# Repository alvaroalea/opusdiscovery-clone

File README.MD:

# The Opus Discovery mini-clone Disk Interface for ZX Spectrum

UNDER LICENSE GPL Version 3

the schematic and PCB for this interfaz, make in KICAD
target is to have a PCB is less than 10x10cm so it's very cheap.

WARNING - THIS IS WORK IN PROGRESS - NOT TESTED

The Advantage of this interfaz over the original are:

- 4 Banks of ROM, so you can swap between original ROM and Quickdos, selectable by dip-switches, in the roms directory you can found it individually and one file ready to burn into a 28C256 flashrom.

- Included Fixed for +2A/+3, so can be used in any ZX Spectrum, selection by jumpers, compatibility with +2A/+3 is not yet tested.

- Reset Button

- Posibility of use crossed and plain floppy cable, and invert Drive 1 and Drive 2, very usefull if you have a Gotek and a real floppy.
With plain floppy cable you can use up to 4 drives.

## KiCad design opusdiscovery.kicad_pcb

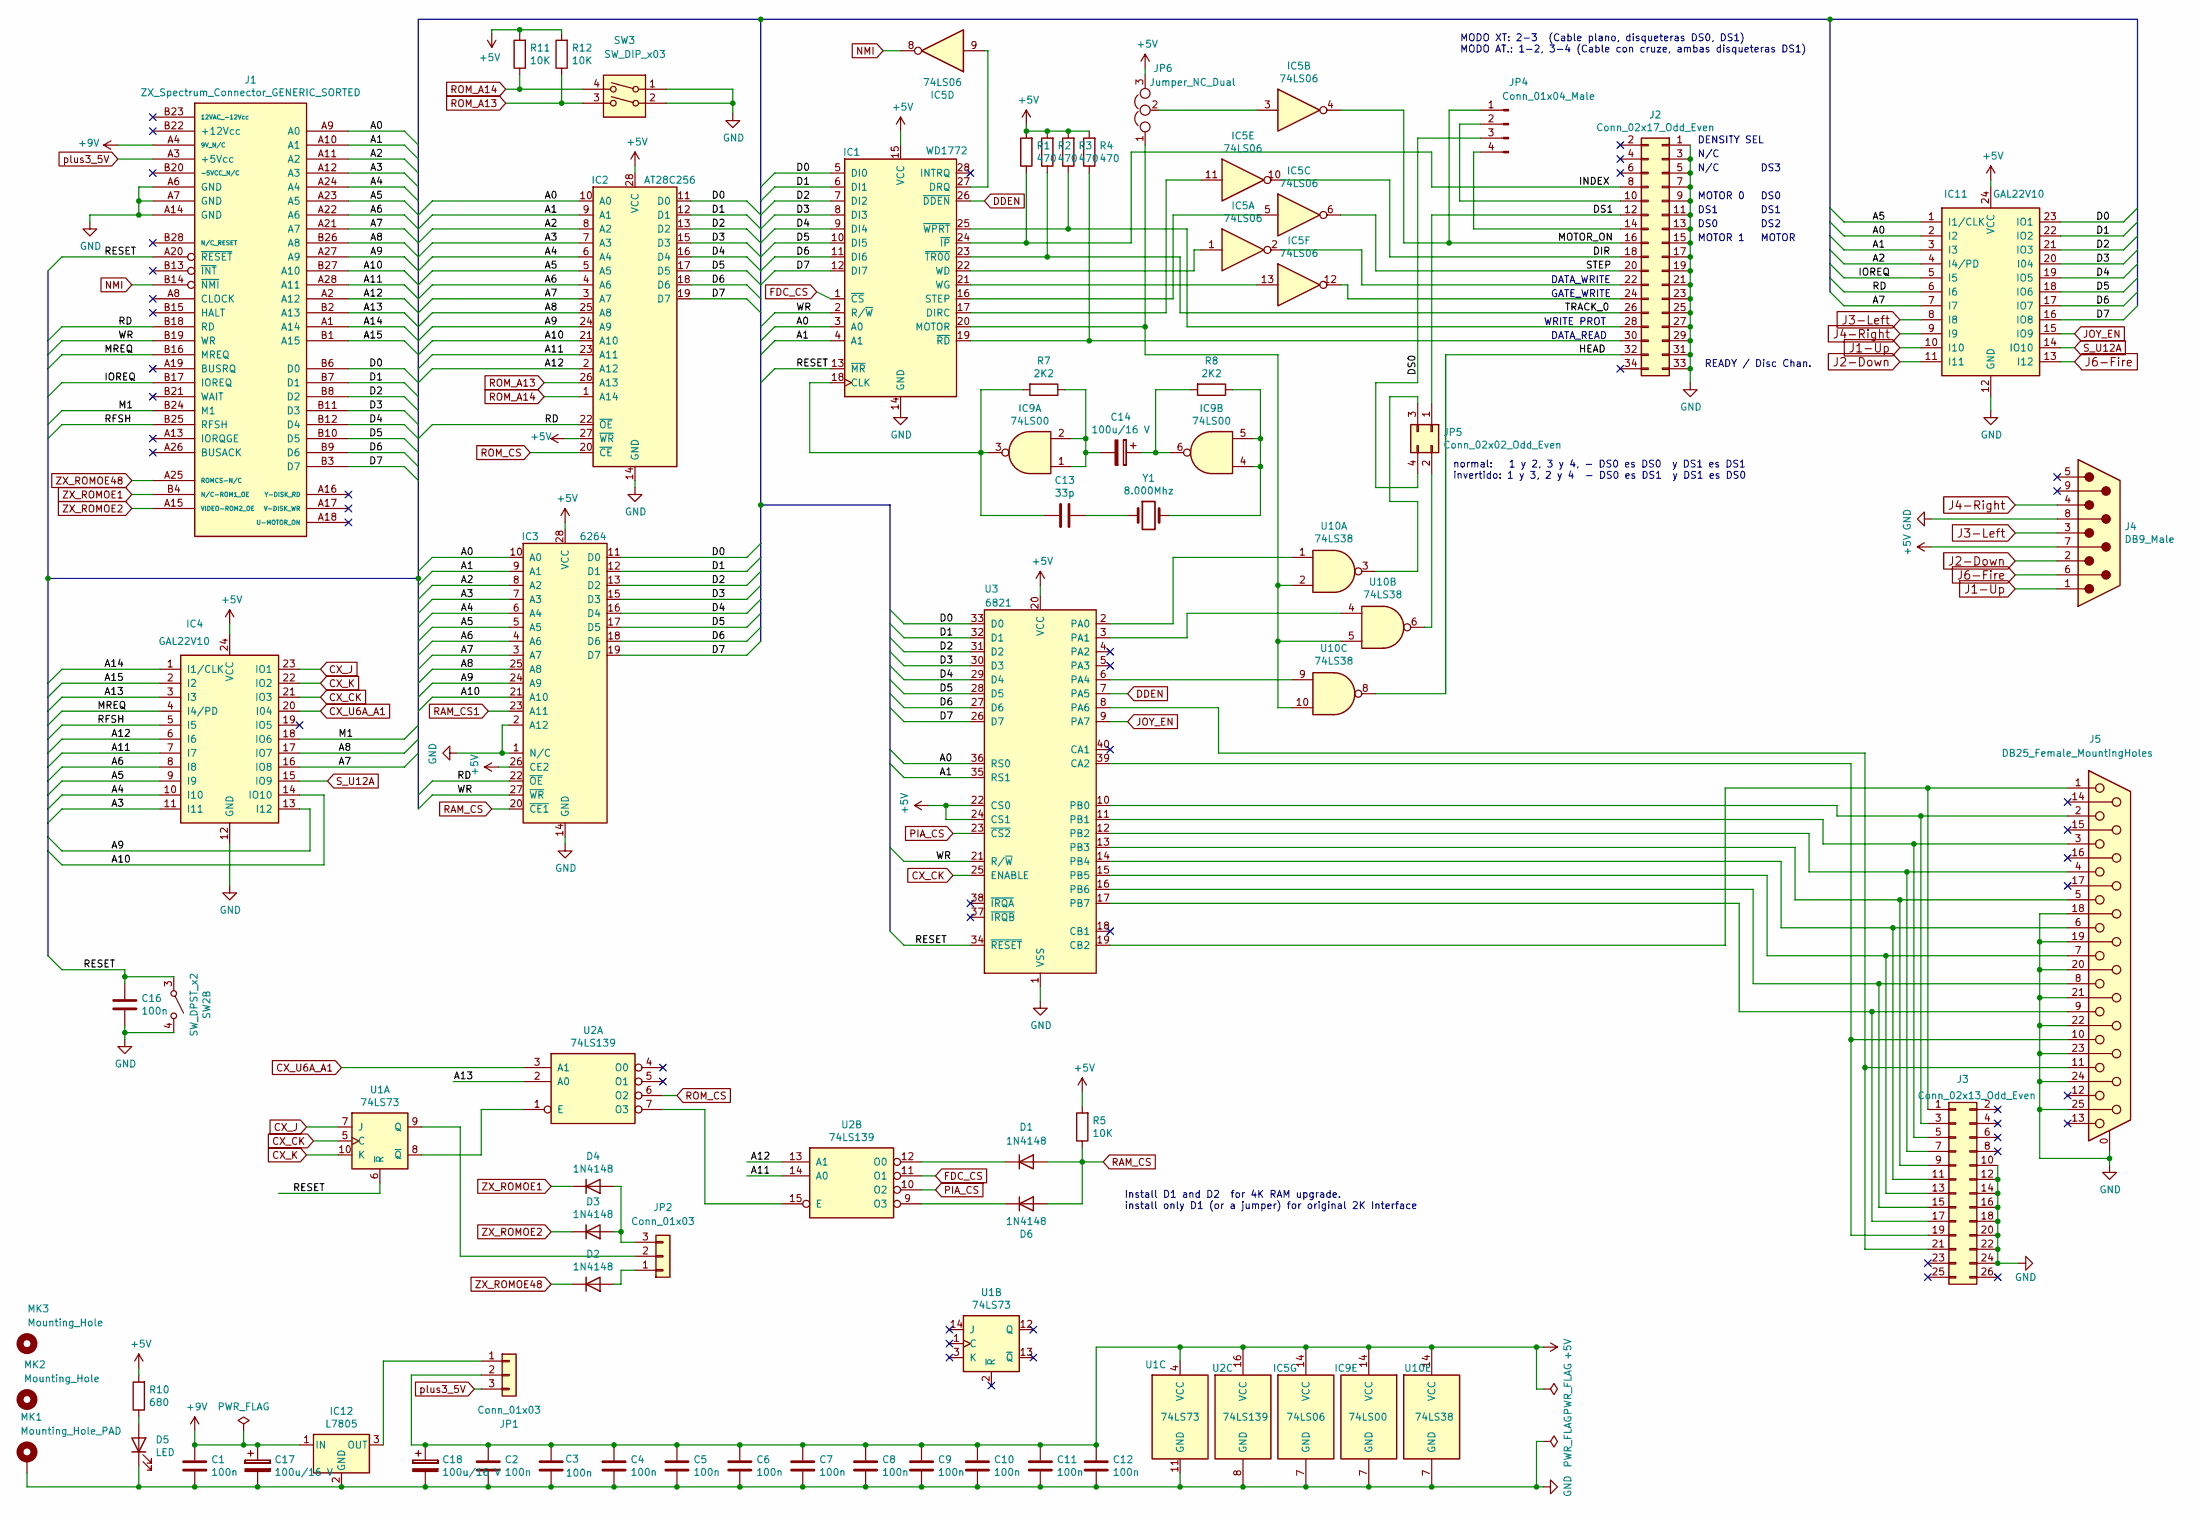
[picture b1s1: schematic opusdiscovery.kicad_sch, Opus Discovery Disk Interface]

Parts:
C1, C2, C3, C4, C5, C6, C7, C8, C9, C10, C11, C12, C16: 100n; C_Disc_D5.0mm_W2.5mm_P5.00mm
C13: 33p; C_Disc_D5.0mm_W2.5mm_P5.00mm
C14, C17, C18: 100u/16 V; CP_Radial_D7.5mm_P2.50mm
D1, D2, D3, D4, D6: 1N4148; D_DO-35_SOD27_P7.62mm_Horizontal
D5: LED; LED_D5.0mm
IC1: WD1772; DIP-28_W15.24mm_LongPads
IC2: AT28C256; DIP-28_W15.24mm_LongPads
IC3: 6264; DIP-28_W15.24mm_LongPads
IC4, IC11: GAL22V10; DIP-24_W7.62mm_LongPads
IC5: 74LS06; DIP-14_W7.62mm_LongPads
IC9: 74LS00; DIP-14_W7.62mm_LongPads
IC12: L7805; TO-220-3_Vertical
J1: ZX_Spectrum_Connector_GENERIC_SORTED; ZX_CONN
J2: Conn_02x17_Odd_Even; PinHeader_2x17_P2.54mm_Vertical
J3: Conn_02x13_Odd_Even; PinHeader_2x13_P2.54mm_Vertical
J4: DB9_Male; DSUB-9_Male_Horizontal_P2.77x2.84mm_EdgePinOffset4.94mm_Hou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
J5: DB25_Female_MountingHoles; DSUB-25_Female_Horizontal_P2.77x2.84mm_EdgePinOffset4.94mm_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
JP1, JP2: Conn_01x03; PinHeader_1x03_P2.54mm_Vertical
JP4: Conn_01x04_Male; PinHeader_1x04_P2.54mm_Vertical
JP5: Conn_02x02_Odd_Even; PinHeader_2x02_P2.54mm_Vertical
JP6: Jumper_NC_Dual; SolderJumper-3_P1.3mm_Bridged12_RoundedPad1.0x1.5mm
MK1: Mounting_Hole_PAD; MountingHole_3mm_Pad_Via
MK2, MK3: Mounting_Hole; MountingHole_3mm
R1, R2, R3, R4: 470; R_Axial_DIN0207_L6.3mm_D2.5mm_P7.62mm_Horizontal
R5, R11, R12: 10K; R_Axial_DIN0207_L6.3mm_D2.5mm_P7.62mm_Horizontal
R7, R8: 2K2; R_Axial_DIN0207_L6.3mm_D2.5mm_P7.62mm_Horizontal
R10: 680; R_Axial_DIN0207_L6.3mm_D2.5mm_P7.62mm_Horizontal
SW2: SW_DPST_x2; SW_TH_Tactile_Omron_B3F-10xx
SW3: SW_DIP_x03; SW_DIP_SPSTx02_Slide_6.7x6.64mm_W7.62mm_P2.54mm_LowProfile
U1: 74LS73; DIP-14_W7.62mm_LongPads
U2: 74LS139; DIP-16_W7.62mm_LongPads
U3: 6821; DIP-40_W15.24mm_LongPads
U10: 74LS38; DIP-14_W7.62mm_LongPads
Y1: 8.000Mhz; Crystal_HC18-U_Vertical

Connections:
+5V: C2.2, C3.2, C4.2, C5.2, C6.2, C7.2, C8.2, C9.2, C10.2, C11.2, C12.2, C18.1, IC1.15 (VCC), IC2.27 (~WR), IC2.28 (VCC), IC3.26 (CE2), IC3.28 (VCC), IC4.24 (VCC), IC5.14 (VCC), IC9.14 (VCC), IC11.24 (VCC), J4.7, JP1.2, JP6.3, R1.2, R2.2, R3.2, R4.2, R5.2, R10.2, R11.2, R12.2, U1.4 (VCC), U2.16 (VCC), U3.20 (VCC), U3.22 (CS0), U3.24 (CS1), U10.14 (VCC)
+9V: C1.2, C17.1, IC12.1 (IN), J1.A4 (9V_N/C)
/A0: IC1.3 (A0), IC2.10 (A0), IC3.10 (A0), IC11.2 (I2), J1.A9 (A0), U3.36 (RS0)
/A1: IC1.4 (A1), IC2.9 (A1), IC3.9 (A1), IC11.3 (I3), J1.A10 (A1), U3.35 (RS1)
/A2: IC2.8 (A2), IC3.8 (A2), IC11.4 (I4/PD), J1.A11 (A2)
/A3: IC2.7 (A3), IC3.7 (A3), IC4.11 (I11), J1.A12 (A3)
/A4: IC2.6 (A4), IC3.6 (A4), IC4.10 (I10), J1.A24 (A4)
/A5: IC2.5 (A5), IC3.5 (A5), IC4.9 (I9), IC11.1 (I1/CLK), J1.A23 (A5)
/A6: IC2.4 (A6), IC3.4 (A6), IC4.8 (I8), J1.A22 (A6)
/A7: IC2.3 (A7), IC3.3 (A7), IC4.16 (IO8), IC11.7 (I7), J1.A21 (A7)
/A8: IC2.25 (A8), IC3.25 (A8), IC4.17 (IO7), J1.B26 (A8)
/A9: IC2.24 (A9), IC3.24 (A9), IC4.13 (I12), J1.A27 (A9)
/A10: IC2.21 (A10), IC3.21 (A10), IC4.14 (IO10), J1.B27 (A10)
/A11: IC2.23 (A11), IC4.7 (I7), J1.A28 (A11), U2.14 (A0)
/A12: IC2.2 (A12), IC4.6 (I6), J1.A2 (A12), U2.13 (A1)
/A13: IC4.3 (I3), J1.B2 (A13), U2.2 (A0)
/A14: IC4.1 (I1/CLK), J1.A1 (A14)
/A15: IC4.2 (I2), J1.B1 (A15)
/D0: IC1.5 (DI0), IC2.11 (D0), IC3.11 (D0), IC11.23 (IO1), J1.B6 (D0), U3.33 (D0)
/D1: IC1.6 (DI1), IC2.12 (D1), IC3.12 (D1), IC11.22 (IO2), J1.B7 (D1), U3.32 (D1)
/D2: IC1.7 (DI2), IC2.13 (D2), IC3.13 (D2), IC11.21 (IO3), J1.B8 (D2), U3.31 (D2)
/D3: IC1.8 (DI3), IC2.15 (D3), IC3.15 (D3), IC11.20 (I04), J1.B11 (D3), U3.30 (D3)
/D4: IC1.9 (DI4), IC2.16 (D4), IC3.16 (D4), IC11.19 (IO5), J1.B12 (D4), U3.29 (D4)
/D5: IC1.10 (DI5), IC2.17 (D5), IC3.17 (D5), IC11.18 (IO6), J1.B10 (D5), U3.28 (D5)
/D6: IC1.11 (DI6), IC2.18 (D6), IC3.18 (D6), IC11.17 (IO7), J1.B9 (D6), U3.27 (D6)
/D7: IC1.12 (DI7), IC2.19 (D7), IC3.19 (D7), IC11.16 (IO8), J1.B3 (D7), U3.26 (D7)
/DIR: IC5.10, J2.18
/DS0: JP4.3, JP5.4
/DS1: J2.12, JP5.1
/HEAD: J2.32, U10.8
/INDEX: IC1.24 (~IP), J2.8, R1.1
/IOREQ: IC11.5 (I5), J1.B17 (IOREQ)
/M1: IC4.18 (IO6), J1.B24 (M1)
/MOTOR_ON: IC5.4, J2.16, JP4.1
/MREQ: IC4.4 (I4/PD), J1.B16 (MREQ)
/RD: IC2.22 (~OE), IC3.22 (~OE), IC11.6 (I6), J1.B18 (RD)
/RESET: C16.2, IC1.13 (~MR), J1.A20 (~RESET), SW2.3 (A), U1.6 (~R), U3.34 (~RESET)
/RFSH: IC4.5 (I5), J1.B25 (RFSH)
/STEP: IC5.6, J2.20
/TRACK_0: IC1.23 (~TR00), J2.26, R2.1
/WR: IC1.2 (R/~W), IC3.27 (~WR), J1.B19 (WR), U3.21 (R/~W)
CX_CK: IC4.21 (IO3), U1.5 (C), U3.25 (ENABLE)
CX_J: IC4.23 (IO1), U1.7 (J)
CX_K: IC4.22 (IO2), U1.10 (K)
CX_U6A_A1: IC4.20 (I04), U2.3 (A1)
DDEN: IC1.26 (~DDEN), U3.7 (PA5)
FDC_CS: IC1.1 (~CS), U2.11 (O1)
GND: C1.1, C2.1, C3.1, C4.1, C5.1, C6.1, C7.1, C8.1, C9.1, C10.1, C11.1, C12.1, C16.1, C17.2, C18.2, D5.1 (K), IC1.14 (GND), IC2.14 (GND), IC3.1 (N/C), IC3.2 (A12), IC3.14 (GND), IC4.12 (GND), IC5.7 (GND), IC9.7 (GND), IC11.12 (GND), IC12.2 (GND), J1.A6 (GND), J1.A7 (GND), J1.A14 (GND), J2.1, J2.3, J2.5, J2.7, J2.9, J2.11, J2.13, J2.15, J2.17, J2.19, J2.21, J2.23, J2.25, J2.27, J2.29, J2.31, J2.33, J3.10, J3.12, J3.14, J3.16, J3.18, J3.20, J3.22, J3.24, J4.8, J5.0 (PAD), J5.18, J5.19, J5.20, J5.21, J5.22, J5.23, J5.24, J5.25, MK1.1, SW2.4 (B), SW3.1, SW3.2, U1.11 (GND), U2.8 (GND), U3.1 (VSS), U10.7 (GND)
J1-Up: IC11.10 (I10), J4.1
J2-Down: IC11.11 (I11), J4.2
J3-Left: IC11.8 (I8), J4.3
J4-Right: IC11.9 (I9), J4.4
J6-Fire: IC11.13 (I12), J4.6
JOY_EN: IC11.15 (IO9), U3.9 (PA7)
NMI: IC5.8, J1.B14 (~NMI)
unnamed: C13.1, Y1.1
unnamed: C13.2, IC1.18 (CLK), IC9.3, R7.2
unnamed: C14.1, IC9.6, R8.2
unnamed: C14.2, IC9.1, IC9.2, R7.1
unnamed: D2.2 (A), JP2.1
unnamed: D3.2 (A), D4.2 (A), JP2.3
unnamed: D5.2 (A), R10.1
unnamed: IC1.16 (STEP), IC5.5
unnamed: IC1.17 (DIRC), IC5.11
unnamed: IC1.19 (~RD), J2.30, R4.1
unnamed: IC1.20 (MOTOR), JP6.1, U10.2, U10.5, U10.10
unnamed: IC1.21 (WG), IC5.13
unnamed: IC1.22 (WD), IC5.1
unnamed: IC1.25 (~WPRT), J2.28, R3.1
unnamed: IC1.27 (DRQ), IC5.9
unnamed: IC5.2, J2.22
unnamed: IC5.3, JP6.2
unnamed: IC5.12, J2.24
unnamed: IC9.4, IC9.5, R8.1, Y1.2
unnamed: IC12.3 (OUT), JP1.1
unnamed: J2.10, JP4.2
unnamed: J2.14, JP4.4
unnamed: J3.1, J5.1, U3.19 (CB2)
unnamed: J3.3, J5.2, U3.10 (PB0)
unnamed: J3.5, J5.3, U3.11 (PB1)
unnamed: J3.7, J5.4, U3.12 (PB2)
unnamed: J3.9, J5.5, U3.13 (PB3)
unnamed: J3.11, J5.6, U3.14 (PB4)
unnamed: J3.13, J5.7, U3.15 (PB5)
unnamed: J3.15, J5.8, U3.16 (PB6)
unnamed: J3.17, J5.9, U3.17 (PB7)
unnamed: J3.19, J5.10, U3.39 (CA2)
unnamed: J3.21, J5.11, U3.8 (PA6)
unnamed: JP2.2, U1.9 (Q)
unnamed: JP5.2, U10.6
unnamed: JP5.3, U10.3
unnamed: U1.8 (~Q), U2.1 (E)
unnamed: U2.7 (O3), U2.15 (E)
unnamed: U3.2 (PA0), U10.1
unnamed: U3.3 (PA1), U10.4
unnamed: U3.6 (PA4), U10.9
PIA_CS: U2.10 (O2), U3.23 (~CS2)
RAM_CS: D1.2 (A), D6.2 (A), IC3.20 (~CE1), R5.1
RAM_CS2: D6.1 (K), U2.9 (O3)
ROM_A13: IC2.26 (A13), R12.1, SW3.3
ROM_A14: IC2.1 (A14), R11.1, SW3.4
ROM_CS: IC2.20 (~CE), U2.6 (O2)
S_U12A: IC4.15 (IO9), IC11.14 (IO10)
ZX_ROMOE1: D4.1 (K), J1.B4 (N/C-ROM1_OE)
ZX_ROMOE2: D3.1 (K), J1.A15 (VIDEO-ROM2_OE)
ZX_ROMOE48: D2.1 (K), J1.A25 (ROMCS-N/C)
plus3_5V: J1.A3 (+5Vcc), JP1.3

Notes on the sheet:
Install D1 and D2 for 4K RAM upgrade. install only D1 (or a jumper) for original 2K Interface
normal: 1 y 2, 3 y 4, - DS0 es DS0 y DS1 es DS1 invertido: 1 y 3, 2 y 4 - DS0 es DS1 y DS1 es DS0
MODO XT: 2-3 (Cable plano, disqueteras DS0, DS1) MODO AT.: 1-2, 3-4 (Cable con cruze, ambas disqueteras DS1)
WRITE PROT
DATA_WRITE
GATE_WRITE
DATA_READ
DENSITY SEL
N/C
MOTOR 0
DS1
DS0
MOTOR 1
READY / Disc Chan.
DS3
DS0
DS2
MOTOR

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
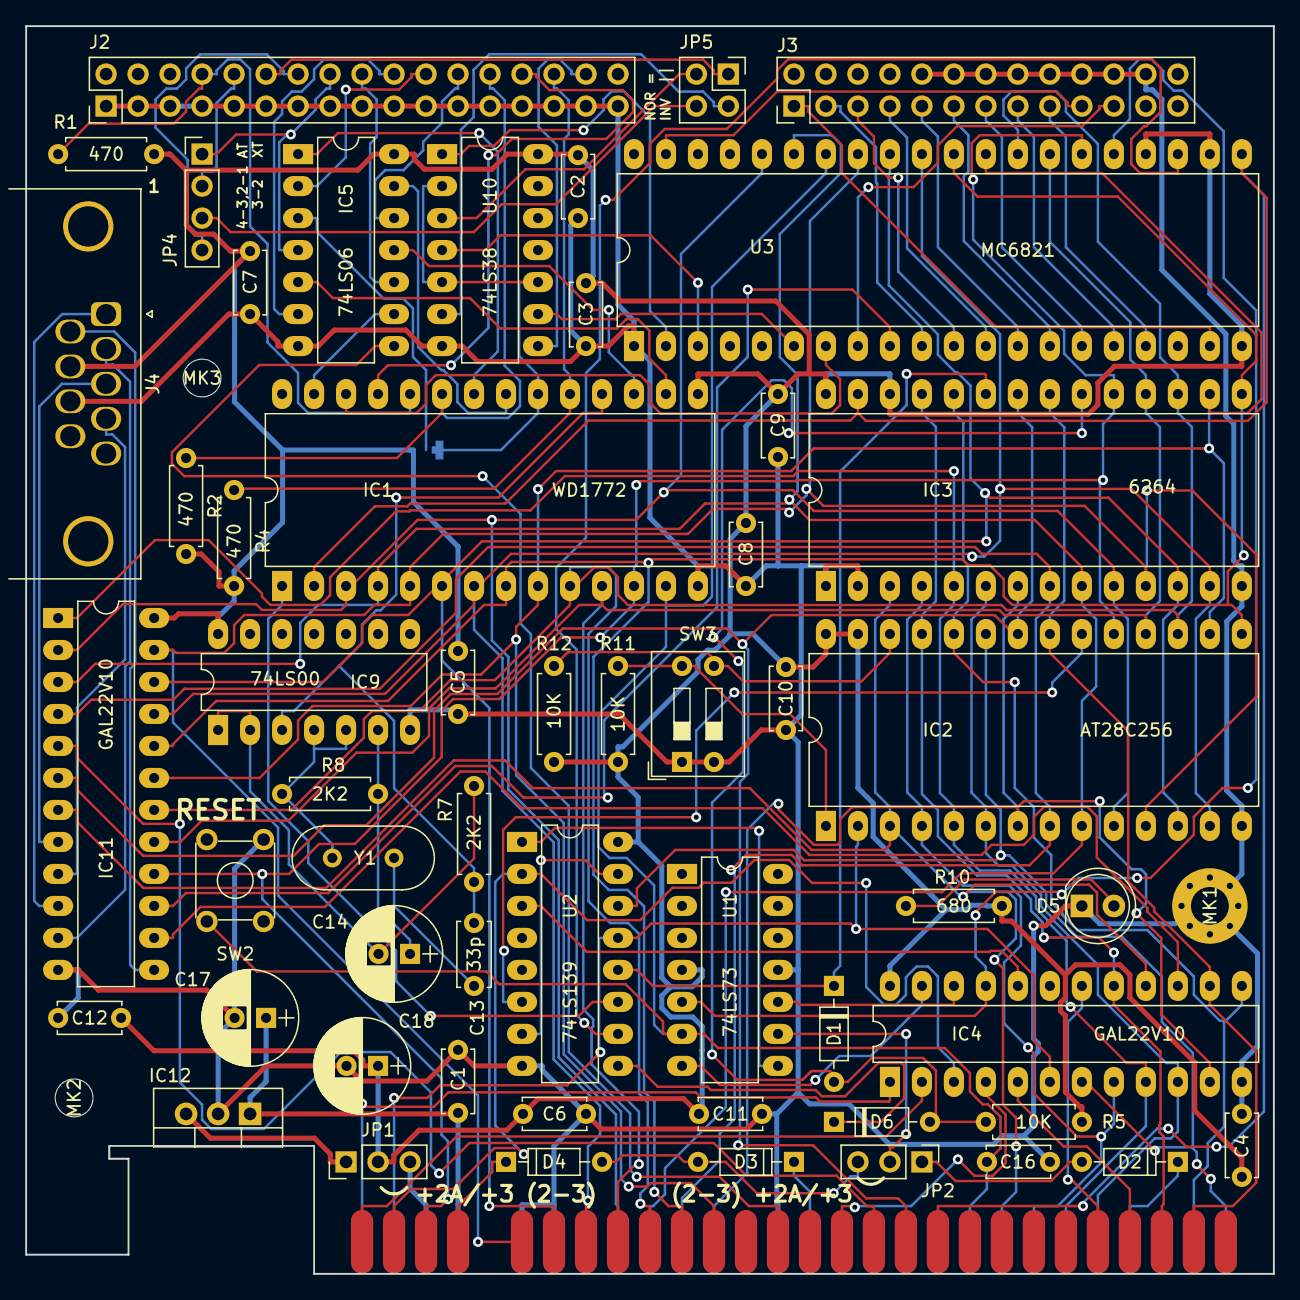
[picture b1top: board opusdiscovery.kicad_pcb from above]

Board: 2 copper layers, 99.1 x 99.1 mm, 59 parts (1 on the bottom side), 108 nets.

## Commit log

2019-03-07 Initial
2019-03-07 typos
2019-03-09 Add preliminary code for GALs
2021-03-26 Update IC11_22V10.PLD
    missing semicolon
2021-04-02 upgrade to kicad 6 and include roms directory
2021-04-02 Compiled files
2021-04-02 update gal equations
2021-04-03 compilation updated
2021-04-03 Corrected typo in A11/A12
2021-04-03 license update
2021-04-03 typo
2021-04-04 another try

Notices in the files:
opusdiscovery.kicad_pcb:
(C) 2019-2021
